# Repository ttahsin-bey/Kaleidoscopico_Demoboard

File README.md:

# Demoboard for LFT's Demo "Kaleidoscopico"

Demos always look better on real hardware. That's what everyone says.

That's why I designed this small circuit board for myself, so that I can run LFT's demo on real hardware instead of just watching it on YouTube. I didn't want to build his version on a stripboard, but preferred a clean solution with SMT components.

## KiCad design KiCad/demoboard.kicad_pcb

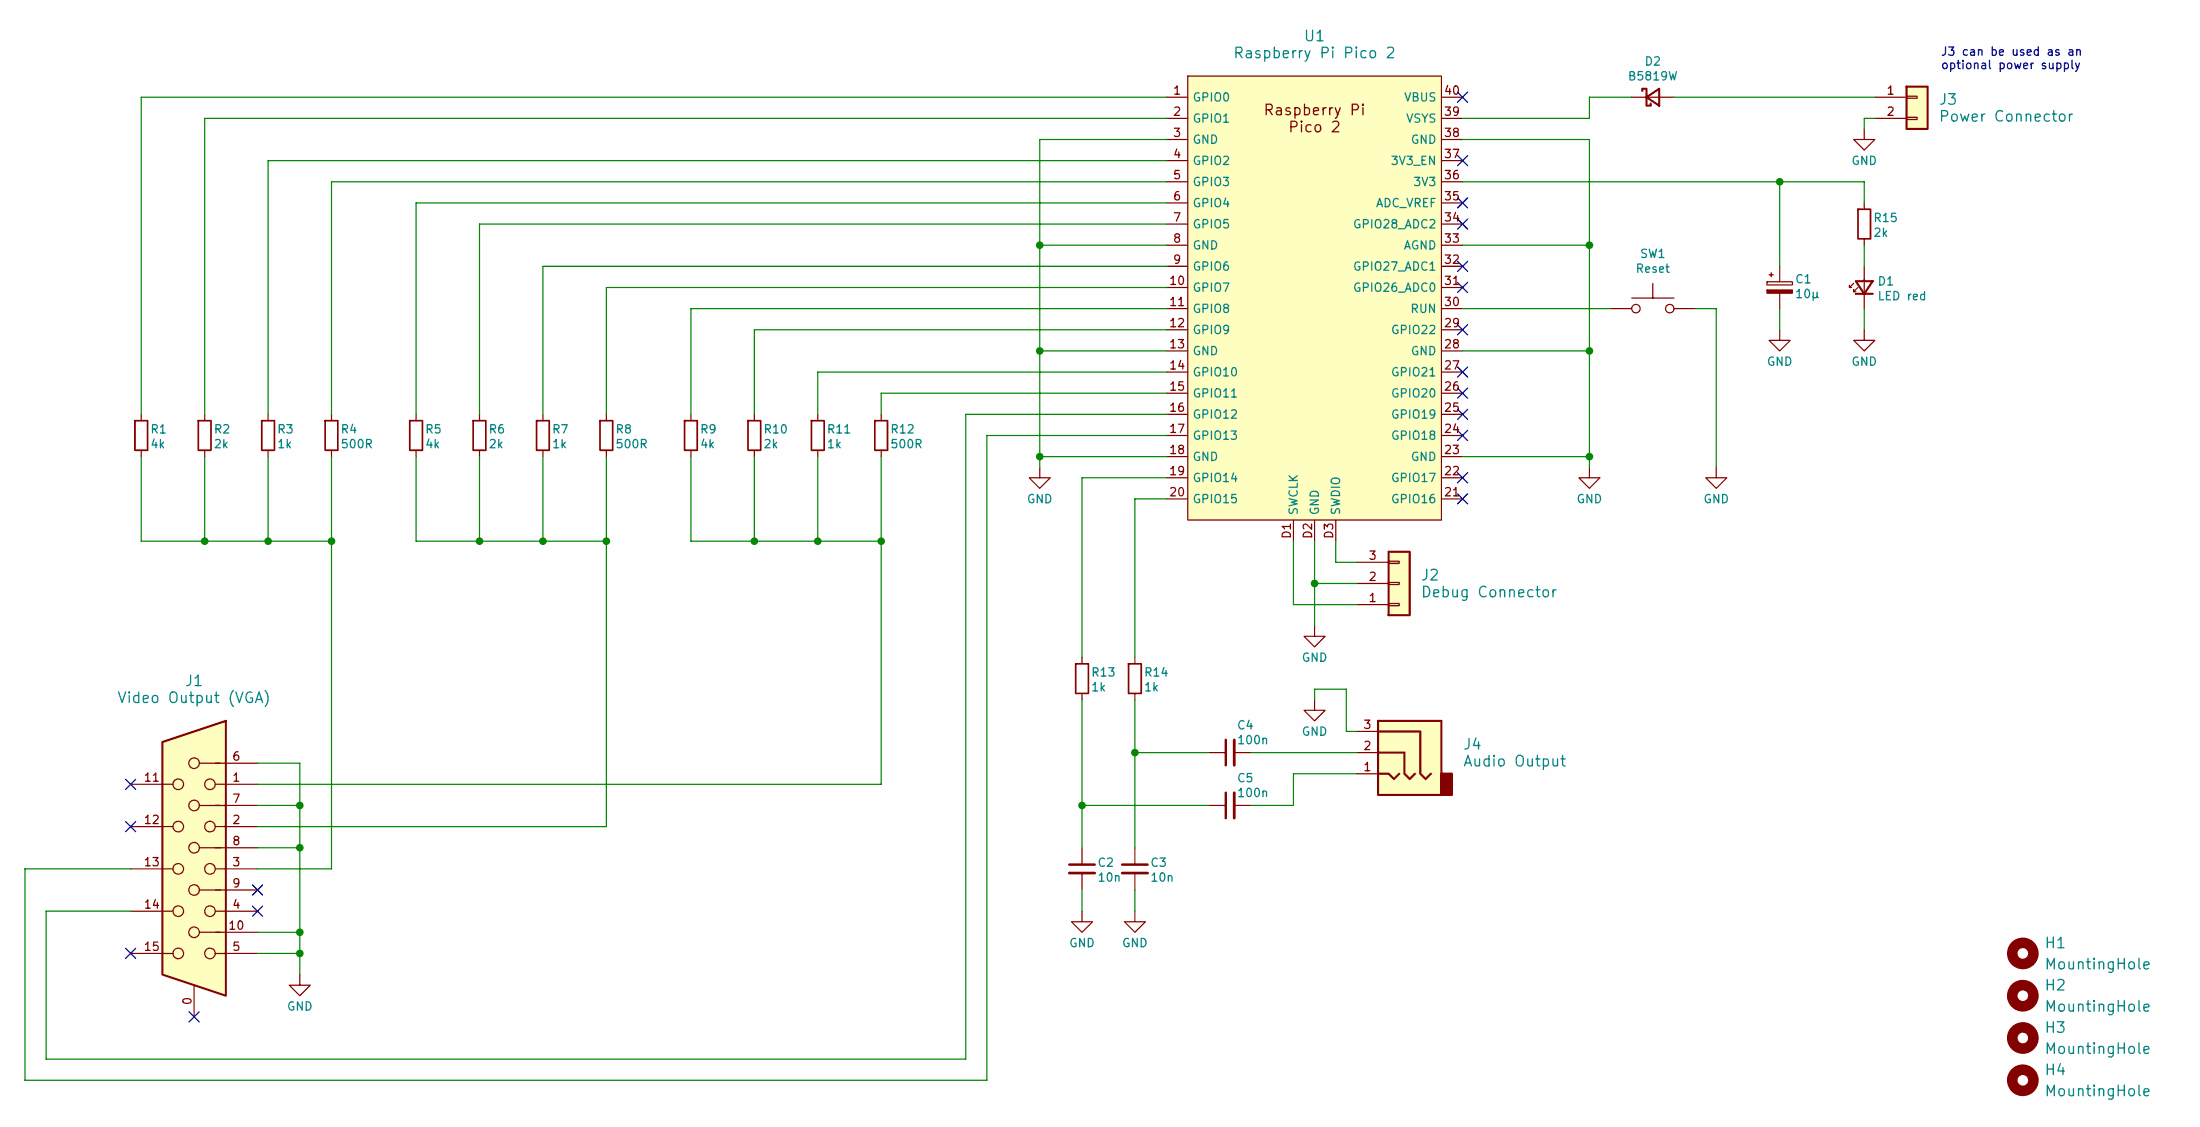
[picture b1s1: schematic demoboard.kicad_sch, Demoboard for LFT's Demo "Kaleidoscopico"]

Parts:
C1: 10µ; CP_Elec_4x5.4; LCSC C264230
C2, C3: 10n; C_0805_2012Metric; LCSC C1710
C4, C5: 100n; C_0805_2012Metric; LCSC C49678
D1: LED red; LED_0805_2012Metric; LCSC C84256
D2: B5819W; TTB_D_SOD-123; LCSC C8598
H1, H2, H3, H4: MountingHole; MountingHole_2.5mm
J1: Video Output (VGA); DSUB-15-HD_Socket_Horizontal_P2.29x2.54mm_EdgePinOffset8.35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; LCSC C711363
J2: Debug Connector; PinHeader_1x03_P2.54mm_Vertical; LCSC C42431836
J3: Power Connector; JST_PH_B2B-PH-K_1x02_P2.00mm_Vertical; LCSC C131337
J4: Audio Output; TTB_Audio; LCSC C711363
R1, R5, R9: 4k; R_0805_2012Metric; LCSC C2828855
R2, R6, R10, R15: 2k; R_0805_2012Metric; LCSC C218483
R3, R7, R11, R13, R14: 1k; R_0805_2012Metric; LCSC C218388
R4, R8, R12: 500R; R_0805_2012Metric; LCSC C2828857
SW1: Reset; TTB_PushbuttonSMD; LCSC C5340123
U1: Raspberry Pi Pico 2; RaspberryPi_Pico_SMD

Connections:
GND: C1.2, C2.2, C3.2, D1.1 (K), J1.5, J1.6, J1.7, J1.8, J1.10, J2.2, J3.2, J4.3, SW1.2, U1.3 (GND), U1.8 (GND), U1.13 (GND), U1.18 (GND), U1.23 (GND), U1.28 (GND), U1.33 (AGND), U1.38 (GND), U1.D2 (GND)
unnamed: C2.1, C5.1, R13.2
unnamed: C3.1, C4.1, R14.2
unnamed: C4.2, J4.2
unnamed: C5.2, J4.1
unnamed: D1.2 (A), R15.2
unnamed: D2.2 (A), J3.1
unnamed: D2.1 (K), U1.39 (VSYS)
unnamed: J1.1, R9.2, R10.2, R11.2, R12.2
unnamed: J1.2, R5.2, R6.2, R7.2, R8.2
unnamed: J1.3, R1.2, R2.2, R3.2, R4.2
unnamed: J2.1, U1.D1 (SWCLK)
unnamed: J2.3, U1.D3 (SWDIO)
unnamed: C1.1, R15.1, U1.36 (3V3)
unnamed: R1.1, U1.1 (GPIO0)
unnamed: R2.1, U1.2 (GPIO1)
unnamed: R3.1, U1.4 (GPIO2)
unnamed: R4.1, U1.5 (GPIO3)
unnamed: R5.1, U1.6 (GPIO4)
unnamed: R6.1, U1.7 (GPIO5)
unnamed: R7.1, U1.9 (GPIO6)
unnamed: R8.1, U1.10 (GPIO7)
unnamed: R9.1, U1.11 (GPIO8)
unnamed: R10.1, U1.12 (GPIO9)
unnamed: R11.1, U1.14 (GPIO10)
unnamed: R12.1, U1.15 (GPIO11)
unnamed: J1.14, U1.16 (GPIO12)
unnamed: J1.13, U1.17 (GPIO13)
unnamed: R13.1, U1.19 (GPIO14)
unnamed: R14.1, U1.20 (GPIO15)
unnamed: SW1.1, U1.30 (RUN)

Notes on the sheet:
J3 can be used as an optional power supply

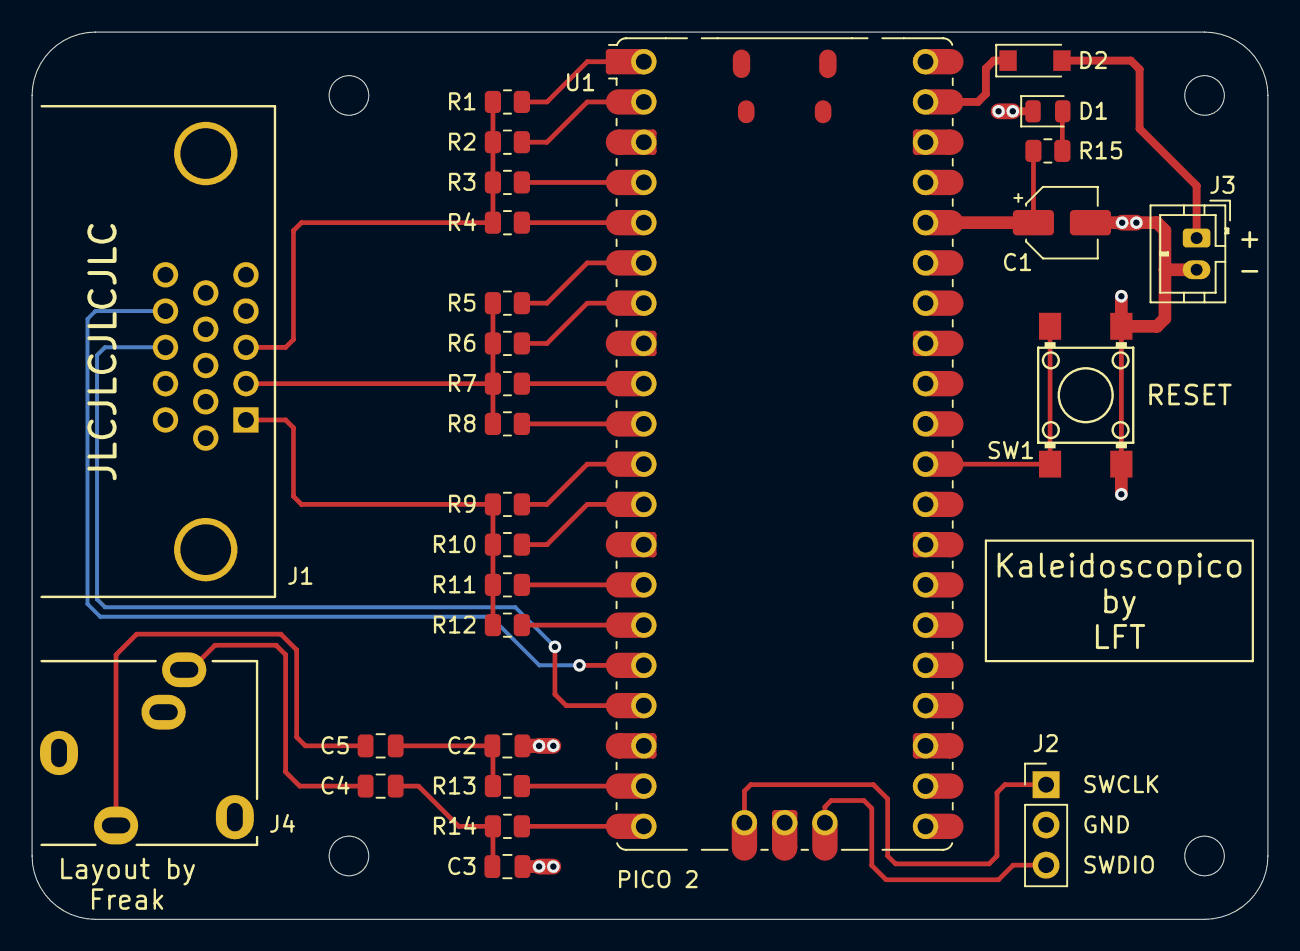
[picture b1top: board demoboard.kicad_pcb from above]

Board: 2 copper layers, 78.0 x 56.0 mm, 32 parts (0 on the bottom side), 31 nets.

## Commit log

2025-09-20 Readme updated
2025-09-20 Readme updated (typos corrected)
2025-09-20 Production files added
2025-09-27 Circuit Diagram added
